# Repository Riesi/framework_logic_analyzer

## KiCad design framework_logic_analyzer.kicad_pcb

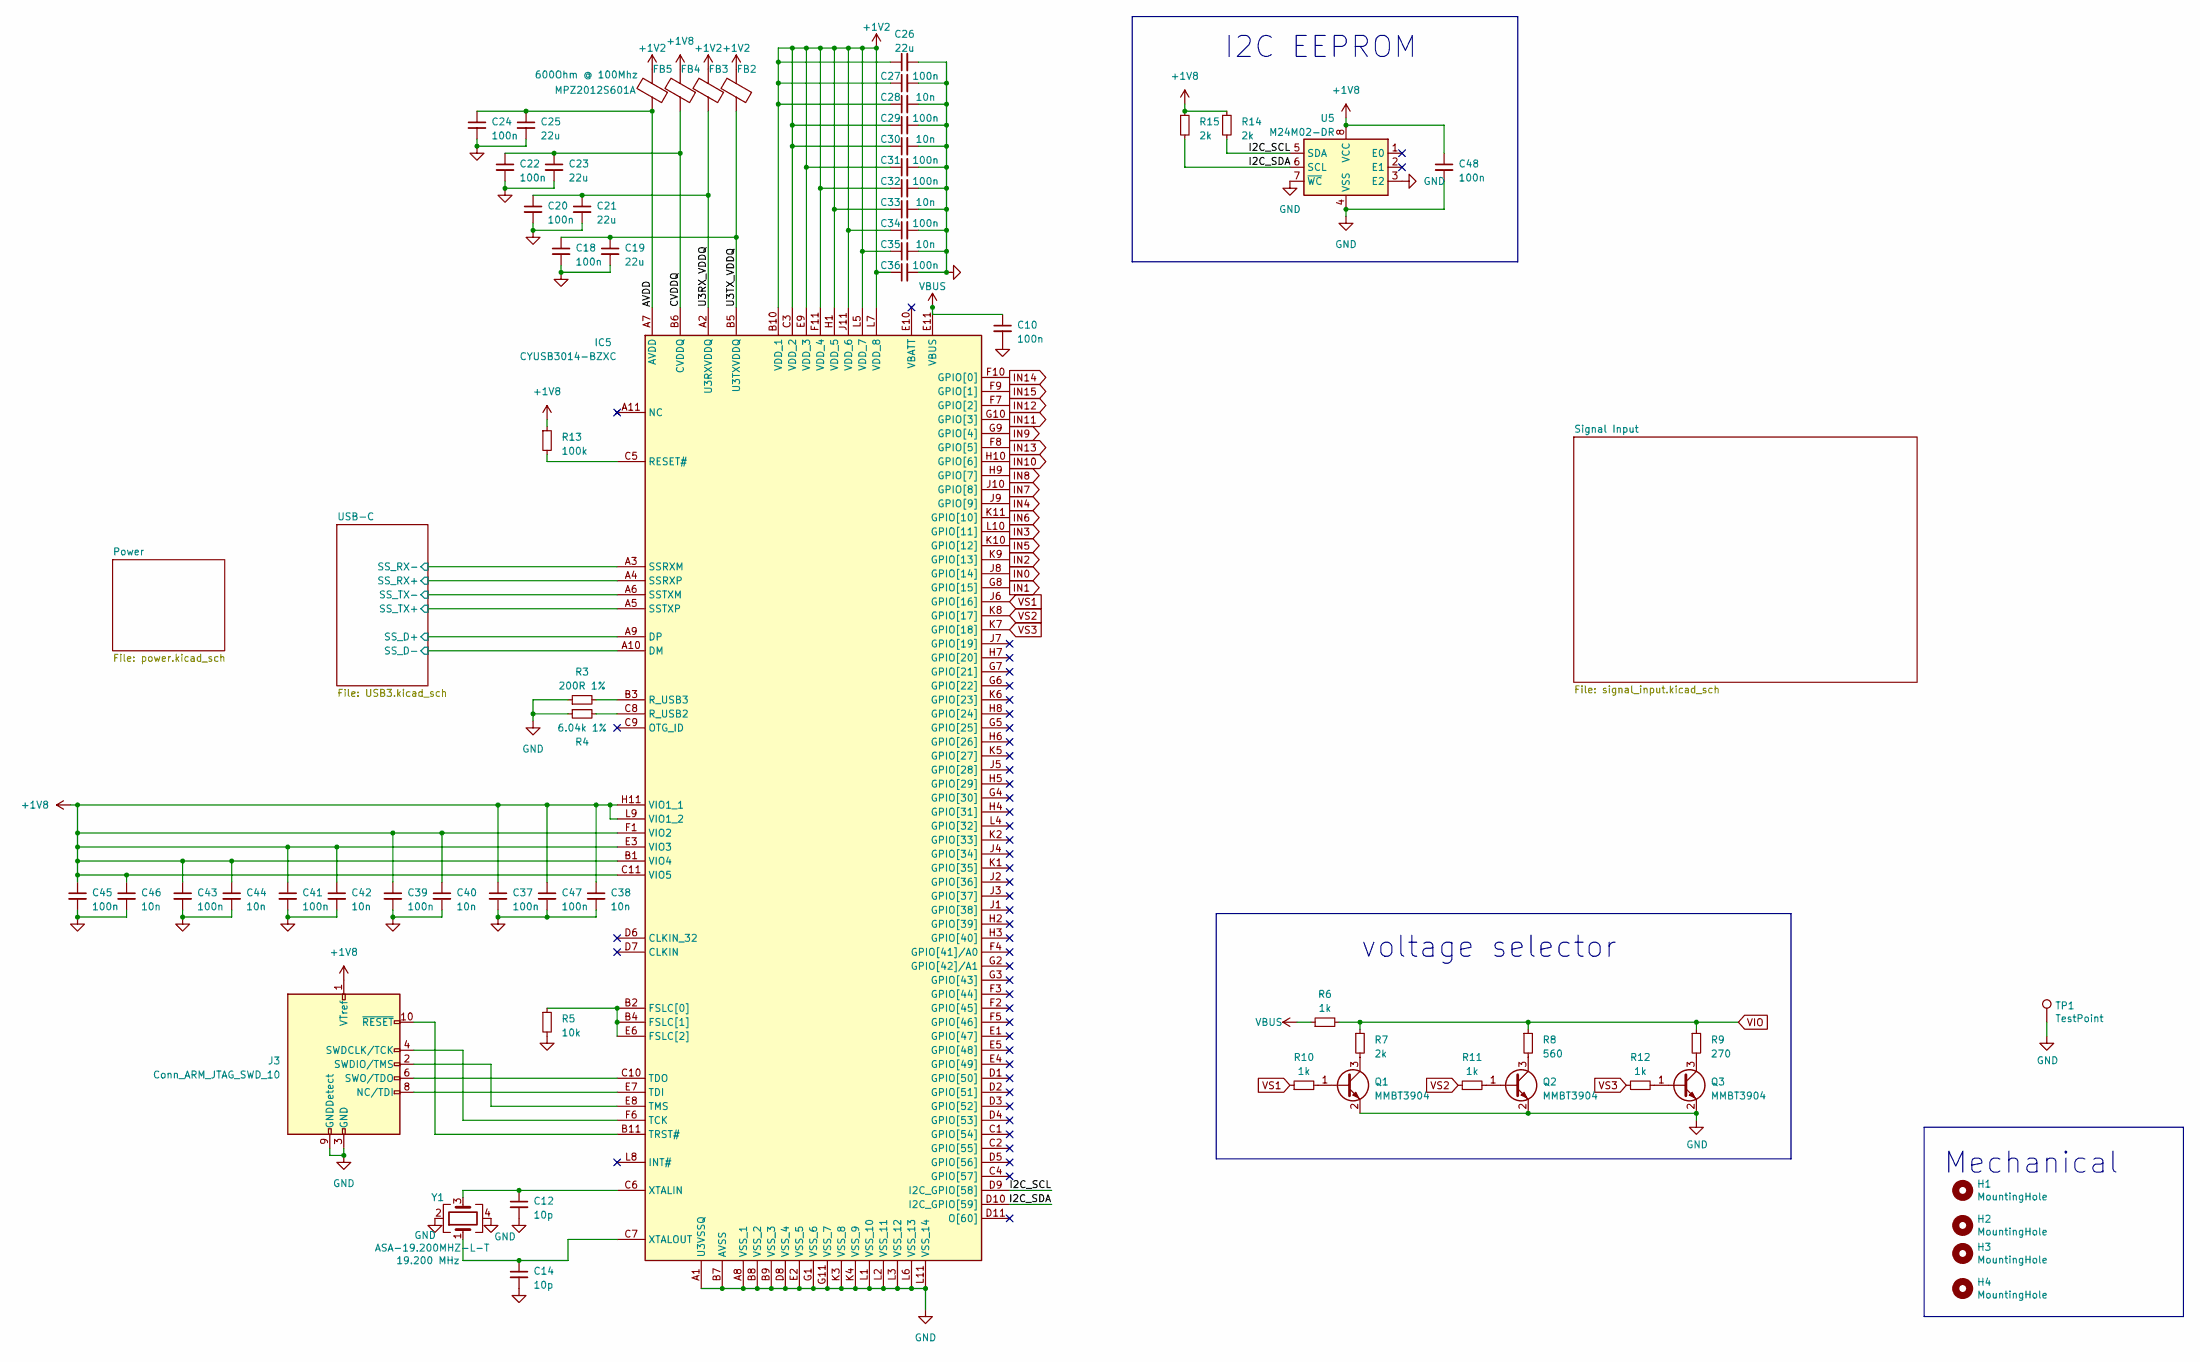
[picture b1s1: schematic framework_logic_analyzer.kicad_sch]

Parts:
C10, C18, C20, C22, C24, C27, C29, C31, C32, C34, C36, C37, C39, C41, C43, C45, C47, C48: 100n; C_0402_1005Metric
C12, C14: 10p; C_0402_1005Metric
C19, C21, C23, C25, C26: 22u; C_0603_1608Metric
C28, C30, C33, C35, C38, C40, C42, C44, C46: 10n; C_0402_1005Metric
FB2, FB3, FB4, FB5: MPZ2012S601A; L_0805_2012Metric
H1, H2, H3, H4: MountingHole; MountingHole_2.2mm_M2
IC5: CYUSB3014-BZXC; BGA121C80P11X11_1000X1000X120; Manufacturer_Part_Number CYUSB3014-BZXC; Mouser Part Number 727-CYUSB3014-BZXC
J3: Conn_ARM_JTAG_SWD_10; PinHeader_2x05_P1.27mm_Vertical
Q1, Q2, Q3: MMBT3904; SOT-23
R3: 200R 1%; R_0402_1005Metric
R4: 6.04k 1%; R_0402_1005Metric
R5: 10k; R_0402_1005Metric
R6, R10, R11, R12: 1k; R_0402_1005Metric
R7, R14, R15: 2k; R_0402_1005Metric
R8: 560; R_0402_1005Metric
R9: 270; R_0402_1005Metric
R13: 100k; R_0402_1005Metric
TP1: TestPoint; TestPoint_Pad_1.5x1.5mm
U5: M24M02-DR; SOIC-8_3.9x4.9mm_P1.27mm
Y1: 19.200 MHz; Crystal_SMD_2016-4Pin_2.0x1.6mm; mpn ASA-19.200MHZ-L-T

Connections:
+1V2: C26.1, C27.1, C28.1, C29.1, C30.1, C31.1, C32.1, C33.1, C34.1, C35.1, C36.1, FB2.2, FB3.2, FB5.2, IC5.B10 (VDD_1), IC5.C3 (VDD_2), IC5.E9 (VDD_3), IC5.F11 (VDD_4), IC5.H1 (VDD_5), IC5.J11 (VDD_6), IC5.L5 (VDD_7), IC5.L7 (VDD_8); also elsewhere on the board
+1V8: C37.1, C38.1, C39.1, C40.1, C41.1, C42.1, C43.1, C44.1, C45.1, C46.1, C47.1, C48.1, FB4.2, IC5.B1 (VIO4), IC5.C11 (VIO5), IC5.E3 (VIO3), IC5.F1 (VIO2), IC5.H11 (VIO1_1), IC5.L9 (VIO1_2), J3.1 (VTref), R13.1, R14.1, R15.1, U5.8 (VCC); also elsewhere on the board
/AVDD: C24.1, C25.1, FB5.1, IC5.A7 (AVDD)
/CVDDQ: C22.1, C23.1, FB4.1, IC5.B6 (CVDDQ)
/I2C_SCL: IC5.D9 (I2C_GPIO[58]), R14.2, U5.5 (SDA)
/I2C_SDA: IC5.D10 (I2C_GPIO[59]), R15.2, U5.6 (SCL)
/U3RX_VDDQ: C20.1, C21.1, FB3.1, IC5.A2 (U3RXVDDQ)
/U3TX_VDDQ: C18.1, C19.1, FB2.1, IC5.B5 (U3TXVDDQ)
/USB-C/SSD+: IC5.A9 (DP); also elsewhere on the board
/USB-C/SSD-: IC5.A10 (DM); also elsewhere on the board
/USB-C/SS_RX+: IC5.A4 (SSRXP); also elsewhere on the board
/USB-C/SS_RX-: IC5.A3 (SSRXM); also elsewhere on the board
/USB-C/SS_TX+: IC5.A5 (SSTXP); also elsewhere on the board
/USB-C/SS_TX-: IC5.A6 (SSTXM); also elsewhere on the board
GND: C10.2, C12.2, C14.2, C18.2, C19.2, C20.2, C21.2, C22.2, C23.2, C24.2, C25.2, C26.2, C27.2, C28.2, C29.2, C30.2, C31.2, C32.2, C33.2, C34.2, C35.2, C36.2, C37.2, C38.2, C39.2, C40.2, C41.2, C42.2, C43.2, C44.2, C45.2, C46.2, C47.2, C48.2, IC5.A1 (U3VSSQ), IC5.A8 (VSS_1), IC5.B7 (AVSS), IC5.B8 (VSS_2), IC5.B9 (VSS_3), IC5.D8 (VSS_4), IC5.E2 (VSS_5), IC5.G1 (VSS_6), IC5.G11 (VSS_7), IC5.K3 (VSS_8), IC5.K4 (VSS_9), IC5.L1 (VSS_10), IC5.L2 (VSS_11), IC5.L3 (VSS_12), IC5.L6 (VSS_13), IC5.L11 (VSS_14), J3.3 (GND), J3.5 (GND), J3.9 (GNDDetect), Q1.2 (E), Q2.2 (E), Q3.2 (E), R3.1, R4.1, R5.2, TP1.1, U5.3 (E2), U5.4 (VSS), U5.7 (~WC), Y1.2, Y1.4; also elsewhere on the board
IN0: IC5.J8 (GPIO[14]); also elsewhere on the board
IN1: IC5.G8 (GPIO[15]); also elsewhere on the board
IN2: IC5.K9 (GPIO[13]); also elsewhere on the board
IN3: IC5.L10 (GPIO[11]); also elsewhere on the board
IN4: IC5.J9 (GPIO[9]); also elsewhere on the board
IN5: IC5.K10 (GPIO[12]); also elsewhere on the board
IN6: IC5.K11 (GPIO[10]); also elsewhere on the board
IN7: IC5.J10 (GPIO[8]); also elsewhere on the board
IN8: IC5.H9 (GPIO[7]); also elsewhere on the board
IN9: IC5.G9 (GPIO[4]); also elsewhere on the board
IN10: IC5.H10 (GPIO[6]); also elsewhere on the board
IN11: IC5.G10 (GPIO[3]); also elsewhere on the board
IN12: IC5.F7 (GPIO[2]); also elsewhere on the board
IN13: IC5.F8 (GPIO[5]); also elsewhere on the board
IN14: IC5.F10 (GPIO[0]); also elsewhere on the board
IN15: IC5.F9 (GPIO[1]); also elsewhere on the board
unnamed: IC5.B2 (FSLC[0]), IC5.B4 (FSLC[1]), IC5.E6 (FSLC[2]), R5.1
unnamed: IC5.C5 (RESET#), R13.2
unnamed: IC5.C8 (R_USB2), R4.2
unnamed: IC5.B3 (R_USB3), R3.2
unnamed: IC5.F6 (TCK), J3.4 (SWDCLK/TCK)
unnamed: IC5.E7 (TDI), J3.8 (NC/TDI)
unnamed: IC5.C10 (TDO), J3.6 (SWO/TDO)
unnamed: IC5.E8 (TMS), J3.2 (SWDIO/TMS)
unnamed: IC5.B11 (TRST#), J3.10 (~RESET)
unnamed: C12.1, IC5.C6 (XTALIN), Y1.3
unnamed: C14.1, IC5.C7 (XTALOUT), Y1.1
unnamed: Q1.1 (B), R10.2
unnamed: Q1.3 (C), R7.2
unnamed: Q2.1 (B), R11.2
unnamed: Q2.3 (C), R8.2
unnamed: Q3.1 (B), R12.2
unnamed: Q3.3 (C), R9.2
VBUS: C10.1, IC5.E11 (VBUS), R6.1; also elsewhere on the board
VIO: R6.2, R7.1, R8.1, R9.1; also elsewhere on the board
VS1: IC5.J6 (GPIO[16]), R10.1
VS2: IC5.K8 (GPIO[17]), R11.1
VS3: IC5.K7 (GPIO[18]), R12.1

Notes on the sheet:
voltage selector
I2C EEPROM
Mechanical

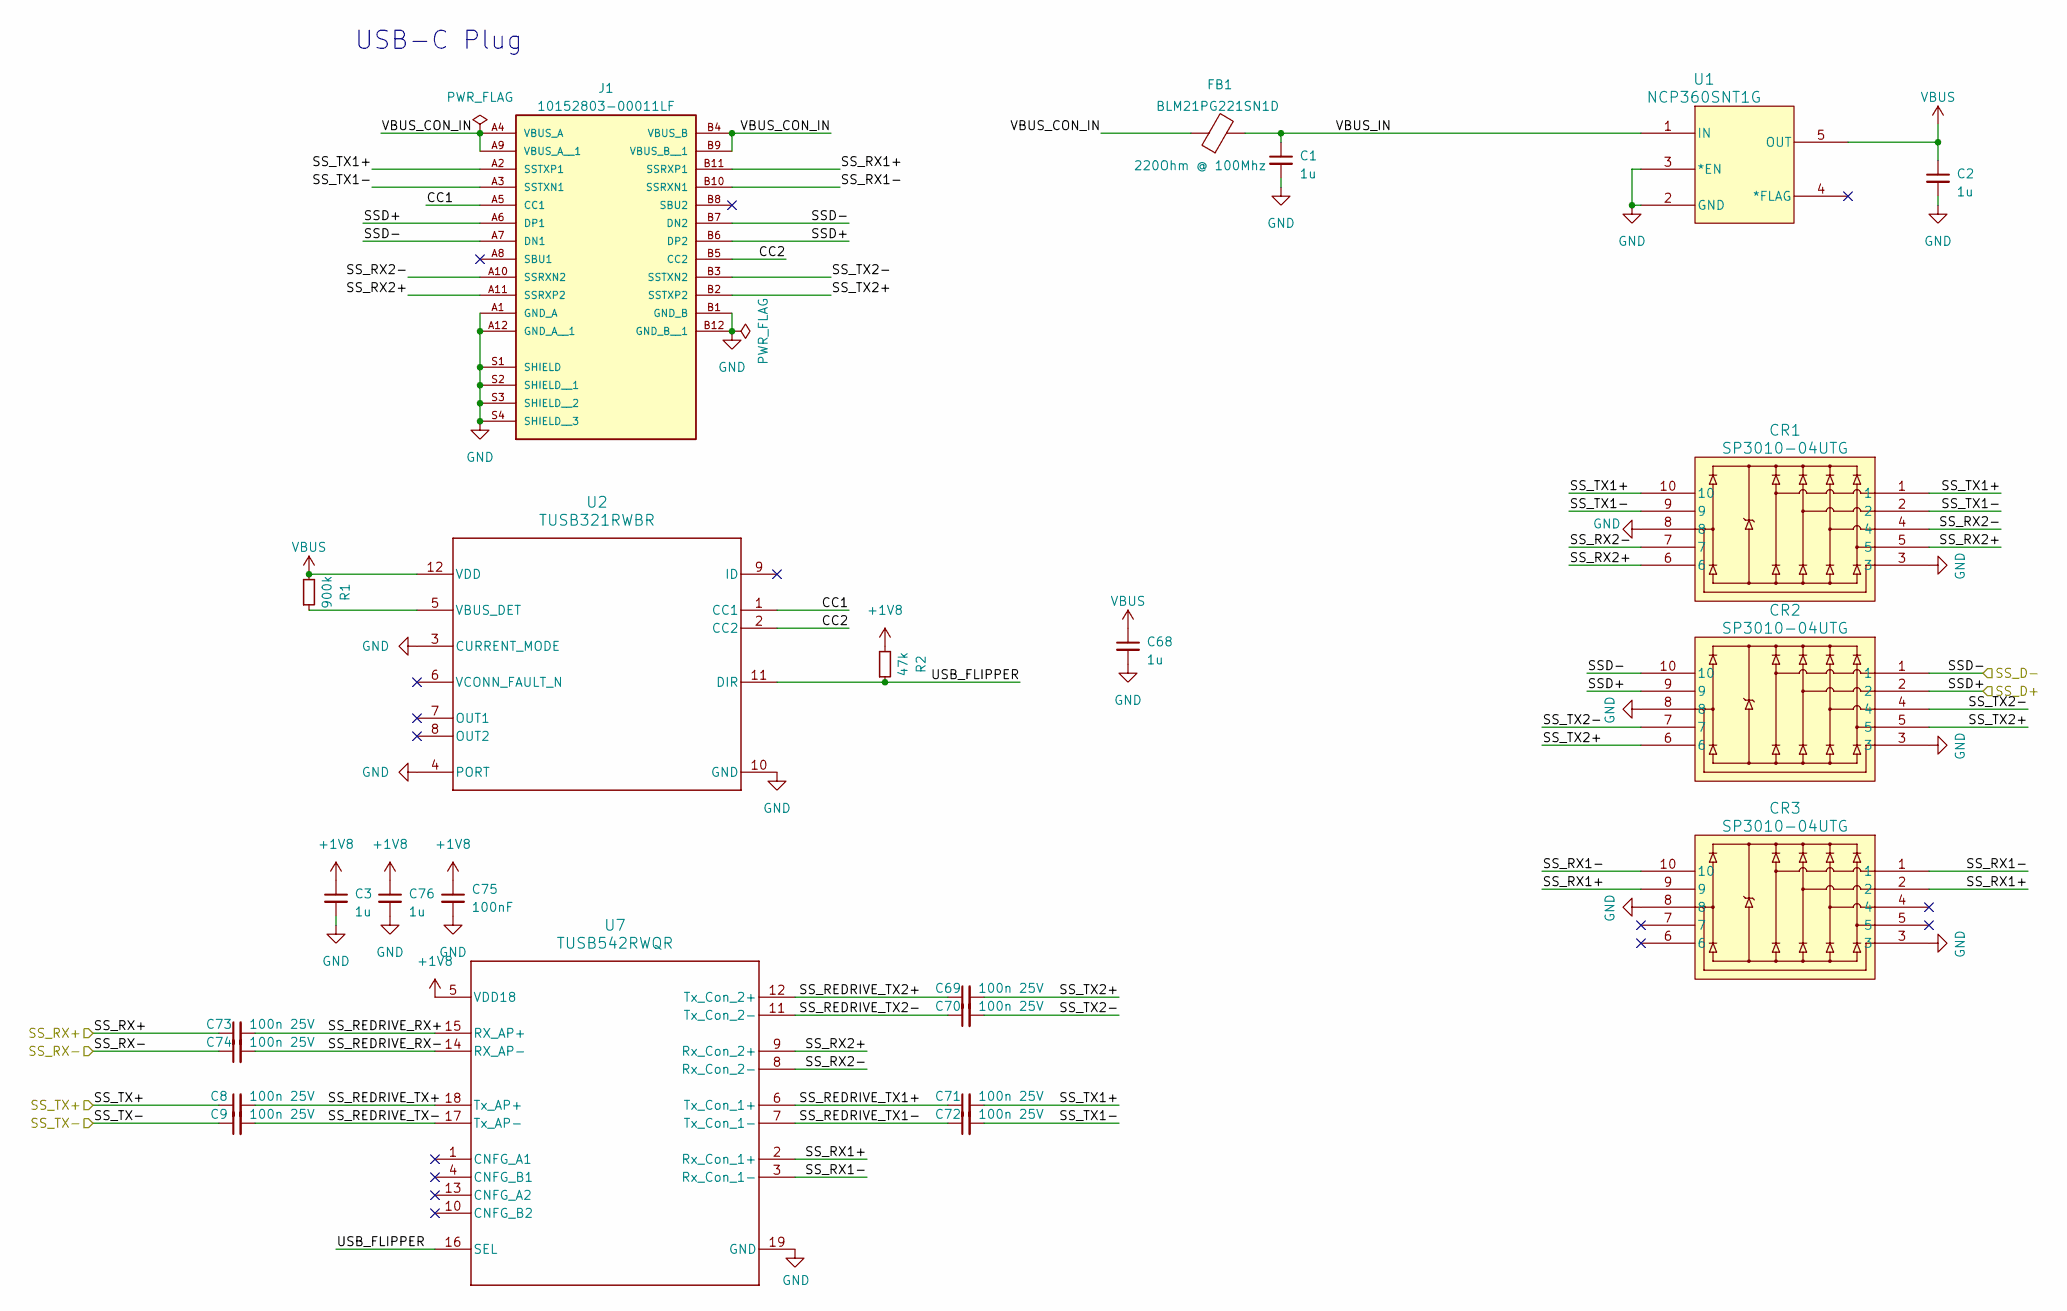
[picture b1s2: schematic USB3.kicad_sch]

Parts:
C1, C2, C3, C68, C76: 1u; C_0402_1005Metric
C8, C9, C69, C70, C71, C72, C73, C74: 100n 25V; C_0201_0603Metric_USB
C75: 100nF; C_0402_1005Metric
CR1, CR2, CR3: SP3010-04UTG; UDFEN-10_MO229_LTF
FB1: BLM21PG221SN1D; L_0805_2012Metric
J1: 10152803-00011LF; 10152803-00011LF_AMPHENOL_10152803-00011LF; PARTREV A
R1: 900k; R_0402_1005Metric
R2: 47k; R_0402_1005Metric
U1: NCP360SNT1G; TSOP5_3X1P5_ONS
U2: TUSB321RWBR; RWB0012A
U7: TUSB542RWQR; RWQ0018A

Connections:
+1V8: C3.1, C75.1, C76.1, R2.2, U7.5 (VDD18); also elsewhere on the board
/USB-C/CC1: J1.A5 (CC1), U2.1 (CC1)
/USB-C/CC2: J1.B5 (CC2), U2.2 (CC2)
/USB-C/SSD+: CR2.2, CR2.9, J1.A6 (DP1), J1.B6 (DP2); also elsewhere on the board
/USB-C/SSD-: CR2.1, CR2.10, J1.A7 (DN1), J1.B7 (DN2); also elsewhere on the board
/USB-C/SS_REDRIVE_RX+: C73.2, U7.15 (RX_AP+)
/USB-C/SS_REDRIVE_RX-: C74.2, U7.14 (RX_AP-)
/USB-C/SS_REDRIVE_TX1+: C71.1, U7.6 (Tx_Con_1+)
/USB-C/SS_REDRIVE_TX1-: C72.1, U7.7 (Tx_Con_1-)
/USB-C/SS_REDRIVE_TX2+: C69.1, U7.12 (Tx_Con_2+)
/USB-C/SS_REDRIVE_TX2-: C70.1, U7.11 (Tx_Con_2-)
/USB-C/SS_REDRIVE_TX+: C8.2, U7.18 (Tx_AP+)
/USB-C/SS_REDRIVE_TX-: C9.2, U7.17 (Tx_AP-)
/USB-C/SS_RX1+: CR3.2, CR3.9, J1.B11 (SSRXP1), U7.2 (Rx_Con_1+)
/USB-C/SS_RX1-: CR3.1, CR3.10, J1.B10 (SSRXN1), U7.3 (Rx_Con_1-)
/USB-C/SS_RX2+: CR1.5, CR1.6, J1.A11 (SSRXP2), U7.9 (Rx_Con_2+)
/USB-C/SS_RX2-: CR1.4, CR1.7, J1.A10 (SSRXN2), U7.8 (Rx_Con_2-)
/USB-C/SS_RX+: C73.1; also elsewhere on the board
/USB-C/SS_RX-: C74.1; also elsewhere on the board
/USB-C/SS_TX1+: C71.2, CR1.1, CR1.10, J1.A2 (SSTXP1)
/USB-C/SS_TX1-: C72.2, CR1.2, CR1.9, J1.A3 (SSTXN1)
/USB-C/SS_TX2+: C69.2, CR2.5, CR2.6, J1.B2 (SSTXP2)
/USB-C/SS_TX2-: C70.2, CR2.4, CR2.7, J1.B3 (SSTXN2)
/USB-C/SS_TX+: C8.1; also elsewhere on the board
/USB-C/SS_TX-: C9.1; also elsewhere on the board
/USB-C/USB_FLIPPER: R2.1, U2.11 (DIR), U7.16 (SEL)
/USB-C/VBUS_CON_IN: FB1.1, J1.A4 (VBUS_A), J1.A9 (VBUS_A__1), J1.B4 (VBUS_B), J1.B9 (VBUS_B__1)
/USB-C/VBUS_IN: C1.1, FB1.2, U1.1 (IN)
GND: C1.2, C2.2, C3.2, C68.2, C75.2, C76.2, CR1.3, CR1.8, CR2.3, CR2.8, CR3.3, CR3.8, J1.A1 (GND_A), J1.A12 (GND_A__1), J1.B1 (GND_B), J1.B12 (GND_B__1), J1.S1 (SHIELD), J1.S2 (SHIELD__1), J1.S3 (SHIELD__2), J1.S4 (SHIELD__3), U1.2 (GND), U1.3 (*EN), U2.3 (CURRENT_MODE), U2.4 (PORT), U2.10 (GND), U7.19 (GND); also elsewhere on the board
unnamed: R1.1, U2.5 (VBUS_DET)
VBUS: C2.1, C68.1, R1.2, U1.5 (OUT), U2.12 (VDD); also elsewhere on the board

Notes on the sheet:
USB-C Plug

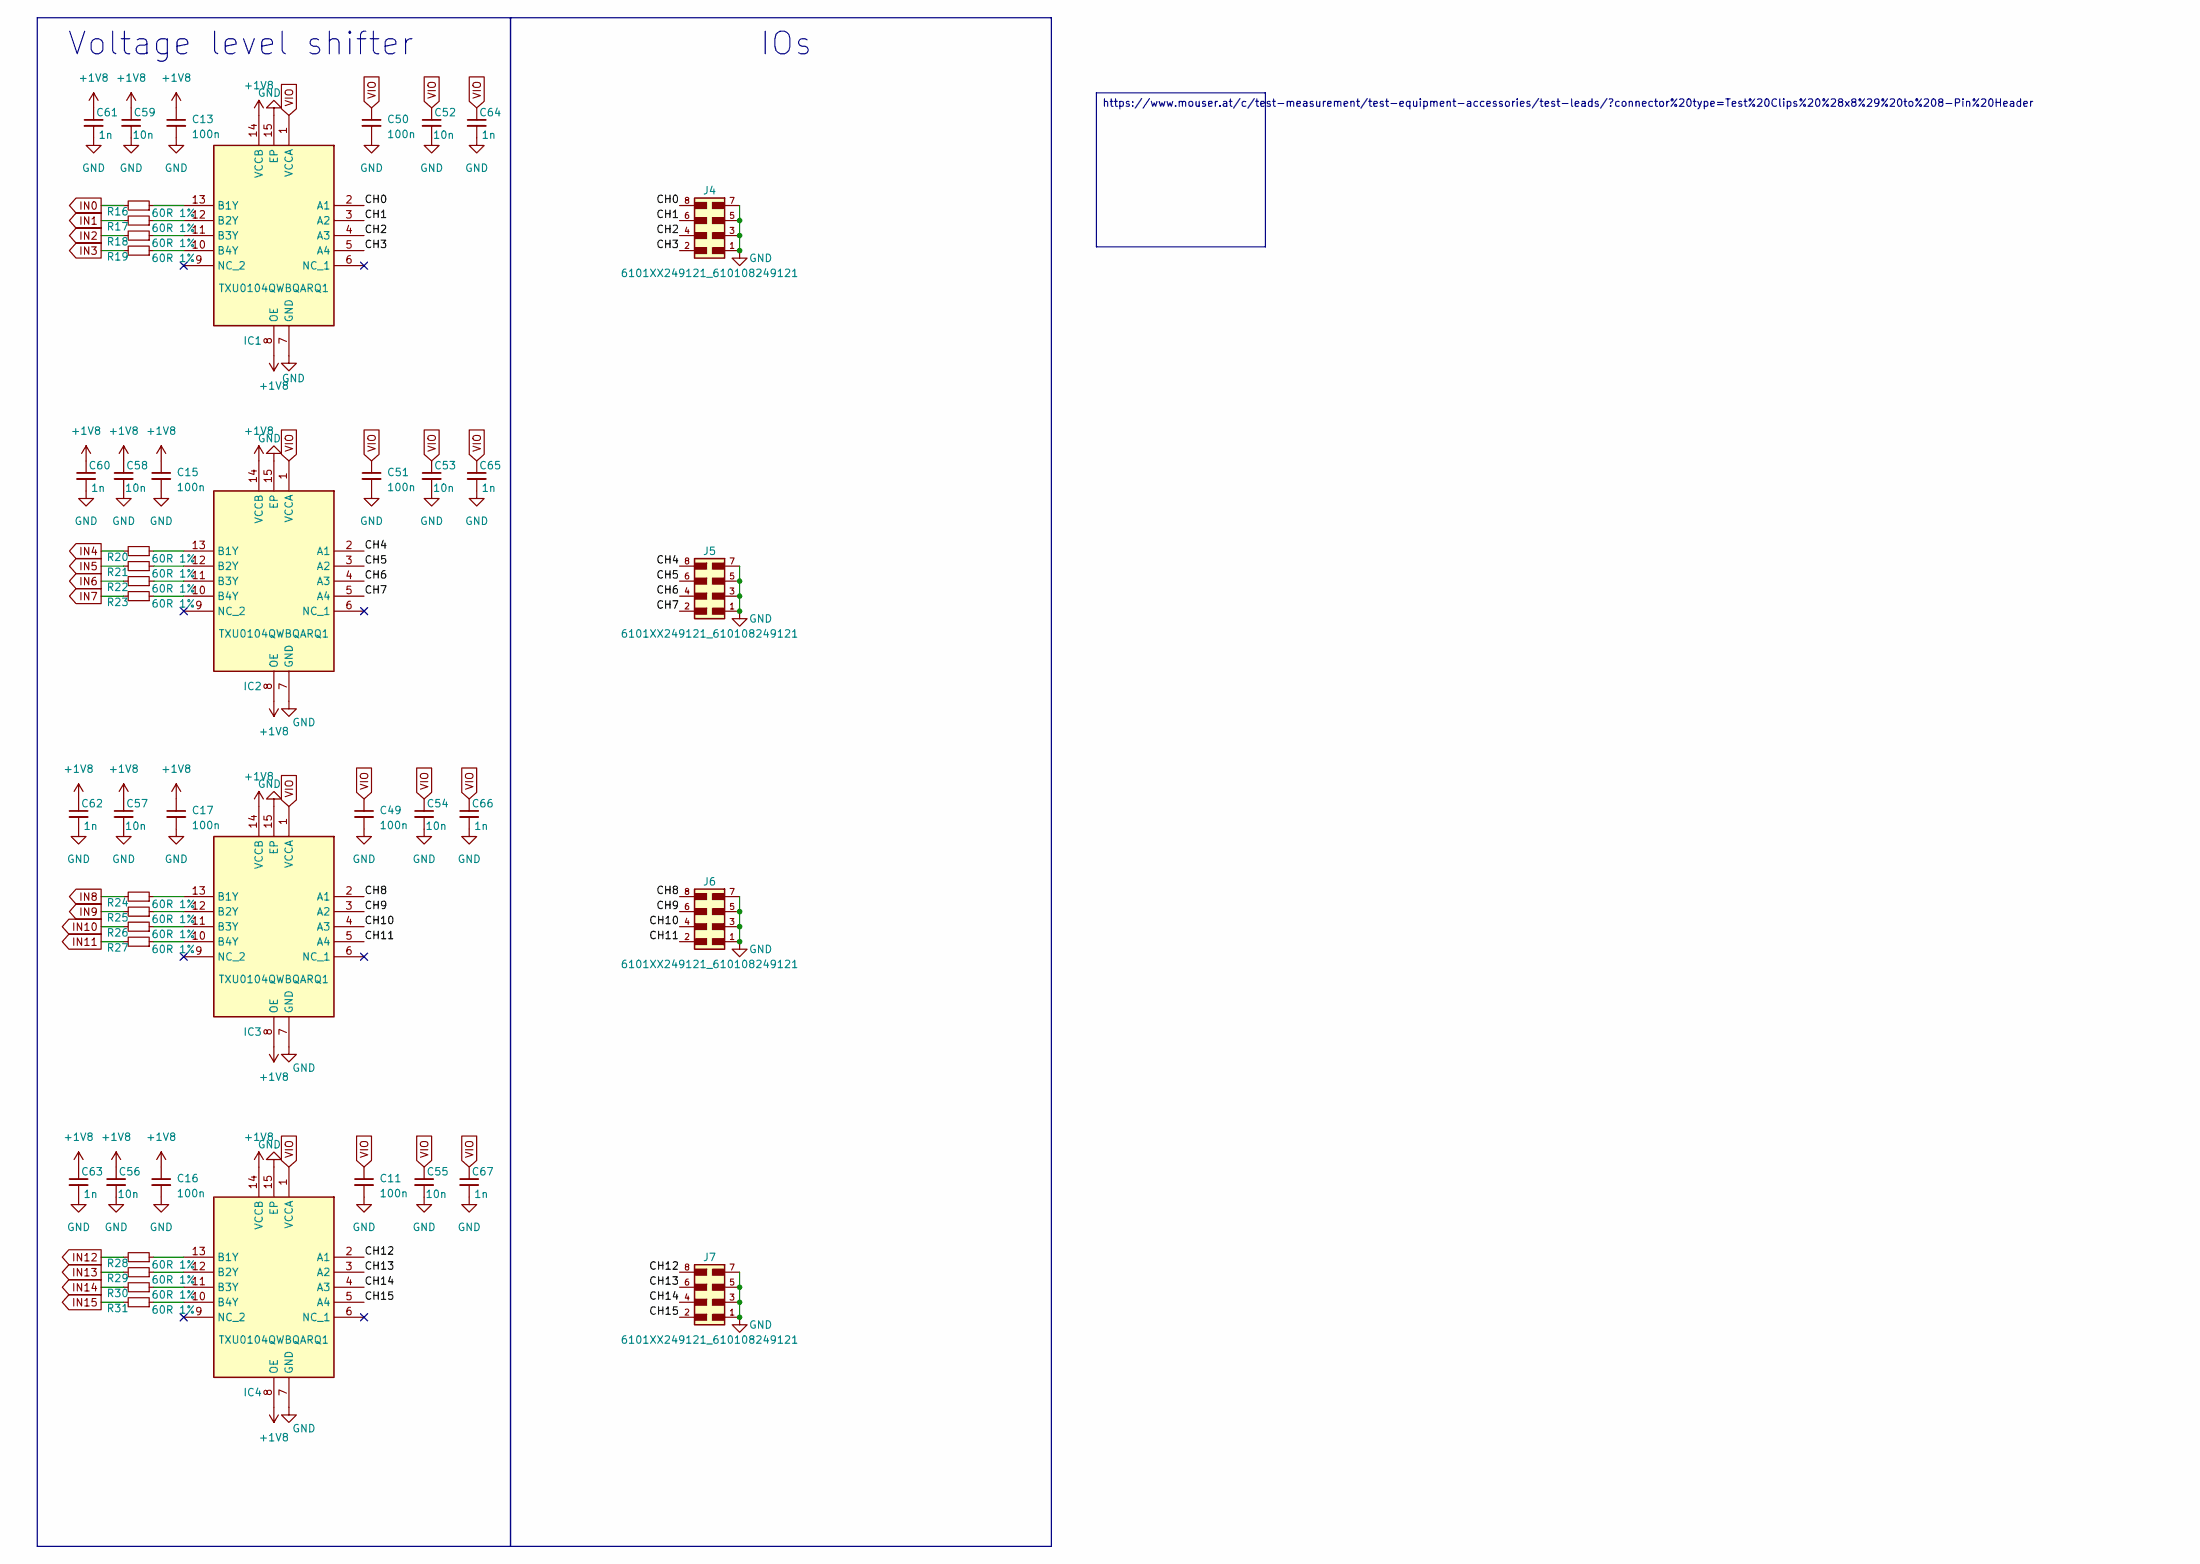
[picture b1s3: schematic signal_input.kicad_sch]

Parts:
C11, C13, C15, C16, C17, C49, C50, C51: 100n; C_0402_1005Metric
C52, C53, C54, C55, C56, C57, C58, C59: 10n; C_0402_1005Metric
C60, C61, C62, C63, C64, C65, C66, C67: 1n; C_0402_1005Metric
IC1, IC2, IC3, IC4: TXU0104QWBQARQ1; Manufacturer_Part_Number TXU0104QWBQARQ1; Mouser Part Number 595-TXU0104QWBQARQ1
J4, J5, J6, J7: 6101XX249121_610108249121; 6101XX249121_610108249121_610108249121
R16, R17, R18, R19, R20, R21, R22, R23, R24, R25, R26, R27, R28, R29, R30, R31: 60R 1%; R_0201_0603Metric_input

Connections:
+1V8: C13.1, C15.1, C16.1, C17.1, C56.1, C57.1, C58.1, C59.1, C60.1, C61.1, C62.1, C63.1, IC1.8 (OE), IC1.14 (VCCB), IC2.8 (OE), IC2.14 (VCCB), IC3.8 (OE), IC3.14 (VCCB), IC4.8 (OE), IC4.14 (VCCB); also elsewhere on the board
/Signal Input/CH0: IC1.2 (A1), J4.8
/Signal Input/CH1: IC1.3 (A2), J4.6
/Signal Input/CH2: IC1.4 (A3), J4.4
/Signal Input/CH3: IC1.5 (A4), J4.2
/Signal Input/CH4: IC2.2 (A1), J5.8
/Signal Input/CH5: IC2.3 (A2), J5.6
/Signal Input/CH6: IC2.4 (A3), J5.4
/Signal Input/CH7: IC2.5 (A4), J5.2
/Signal Input/CH8: IC3.2 (A1), J6.8
/Signal Input/CH9: IC3.3 (A2), J6.6
/Signal Input/CH10: IC3.4 (A3), J6.4
/Signal Input/CH11: IC3.5 (A4), J6.2
/Signal Input/CH12: IC4.2 (A1), J7.8
/Signal Input/CH13: IC4.3 (A2), J7.6
/Signal Input/CH14: IC4.4 (A3), J7.4
/Signal Input/CH15: IC4.5 (A4), J7.2
GND: C11.2, C13.2, C15.2, C16.2, C17.2, C49.2, C50.2, C51.2, C52.2, C53.2, C54.2, C55.2, C56.2, C57.2, C58.2, C59.2, C60.2, C61.2, C62.2, C63.2, C64.2, C65.2, C66.2, C67.2, IC1.7 (GND), IC1.15 (EP), IC2.7 (GND), IC2.15 (EP), IC3.7 (GND), IC3.15 (EP), IC4.7 (GND), IC4.15 (EP), J4.1, J4.3, J4.5, J4.7, J5.1, J5.3, J5.5, J5.7, J6.1, J6.3, J6.5, J6.7, J7.1, J7.3, J7.5, J7.7; also elsewhere on the board
IN0: R16.2; also elsewhere on the board
IN1: R17.2; also elsewhere on the board
IN2: R18.2; also elsewhere on the board
IN3: R19.2; also elsewhere on the board
IN4: R20.2; also elsewhere on the board
IN5: R21.2; also elsewhere on the board
IN6: R22.2; also elsewhere on the board
IN7: R23.2; also elsewhere on the board
IN8: R24.2; also elsewhere on the board
IN9: R25.2; also elsewhere on the board
IN10: R26.2; also elsewhere on the board
IN11: R27.2; also elsewhere on the board
IN12: R28.2; also elsewhere on the board
IN13: R29.2; also elsewhere on the board
IN14: R30.2; also elsewhere on the board
IN15: R31.2; also elsewhere on the board
unnamed: IC1.13 (B1Y), R16.1
unnamed: IC1.12 (B2Y), R17.1
unnamed: IC1.11 (B3Y), R18.1
unnamed: IC1.10 (B4Y), R19.1
unnamed: IC2.13 (B1Y), R20.1
unnamed: IC2.12 (B2Y), R21.1
unnamed: IC2.11 (B3Y), R22.1
unnamed: IC2.10 (B4Y), R23.1
unnamed: IC3.13 (B1Y), R24.1
unnamed: IC3.12 (B2Y), R25.1
unnamed: IC3.11 (B3Y), R26.1
unnamed: IC3.10 (B4Y), R27.1
unnamed: IC4.13 (B1Y), R28.1
unnamed: IC4.12 (B2Y), R29.1
unnamed: IC4.11 (B3Y), R30.1
unnamed: IC4.10 (B4Y), R31.1
VIO: C11.1, C49.1, C50.1, C51.1, C52.1, C53.1, C54.1, C55.1, C64.1, C65.1, C66.1, C67.1, IC1.1 (VCCA), IC2.1 (VCCA), IC3.1 (VCCA), IC4.1 (VCCA); also elsewhere on the board

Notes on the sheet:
Voltage level shifter
IOs
https://www.mouser.at/c/test-measurement/test-equipment-accessories/test-leads/?connector%20type=Test%20Clips%20%28x8%29%20to%208-Pin%20Header

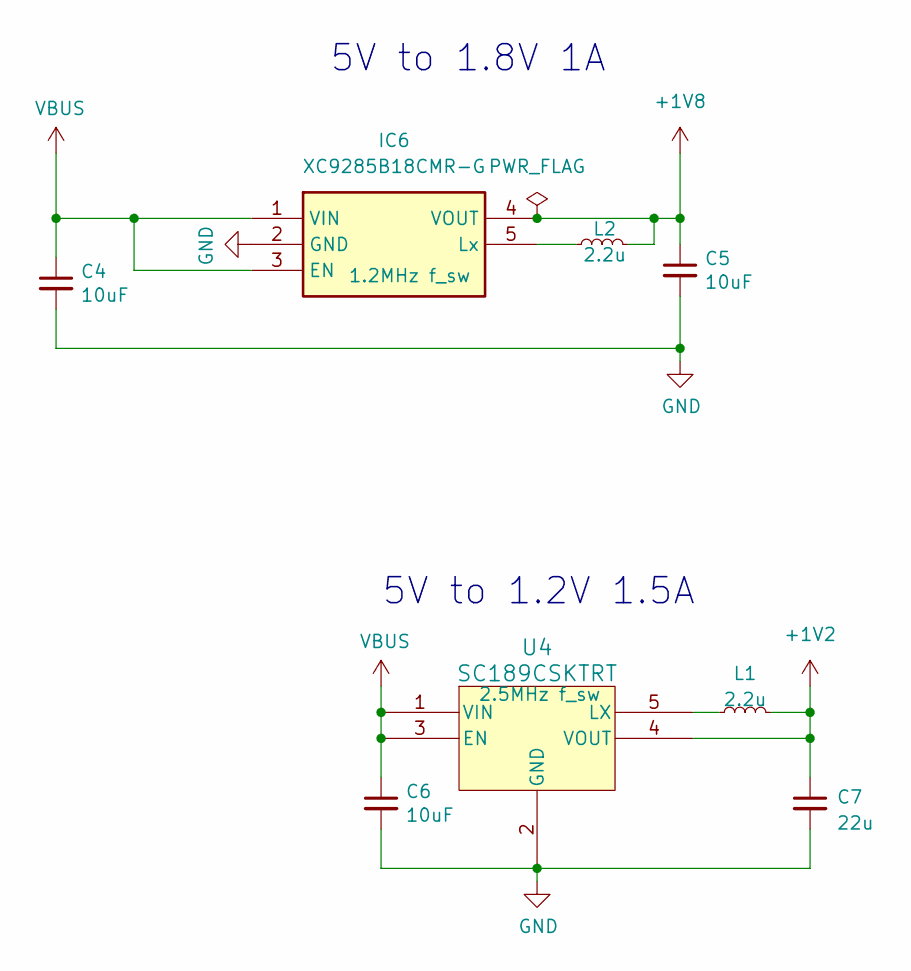
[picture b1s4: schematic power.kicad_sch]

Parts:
C4, C5, C6: 10uF; C_0805_2012Metric
C7: 22u; C_0603_1608Metric
IC6: XC9285B18CMR-G; SOT95P280X130-5N; Manufacturer_Part_Number XC9285B18CMR-G
L1, L2: 2.2u; L_1008_2520Metric; LCSC C315721
U4: SC189CSKTRT; SOT_CSKTRT_SEM

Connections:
+1V2: C7.1, L1.2, U4.4 (VOUT); also elsewhere on the board
+1V8: C5.1, IC6.4 (VOUT), L2.2; also elsewhere on the board
GND: C4.2, C5.2, C6.2, C7.2, IC6.2 (GND), U4.2 (GND); also elsewhere on the board
unnamed: IC6.5 (Lx), L2.1
unnamed: L1.1, U4.5 (LX)
VBUS: C4.1, C6.1, IC6.1 (VIN), IC6.3 (EN), U4.1 (VIN), U4.3 (EN); also elsewhere on the board

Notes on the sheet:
5V to 1.8V 1A
5V to 1.2V 1.5A

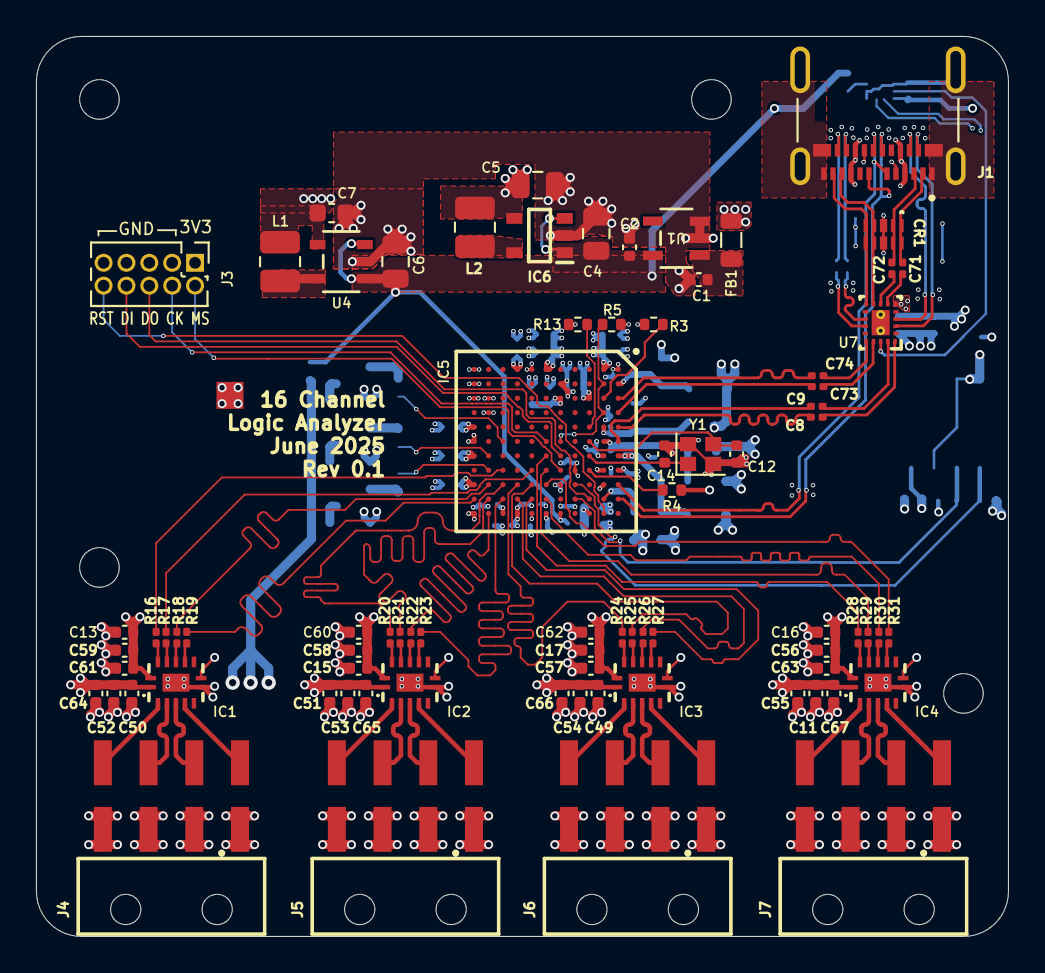
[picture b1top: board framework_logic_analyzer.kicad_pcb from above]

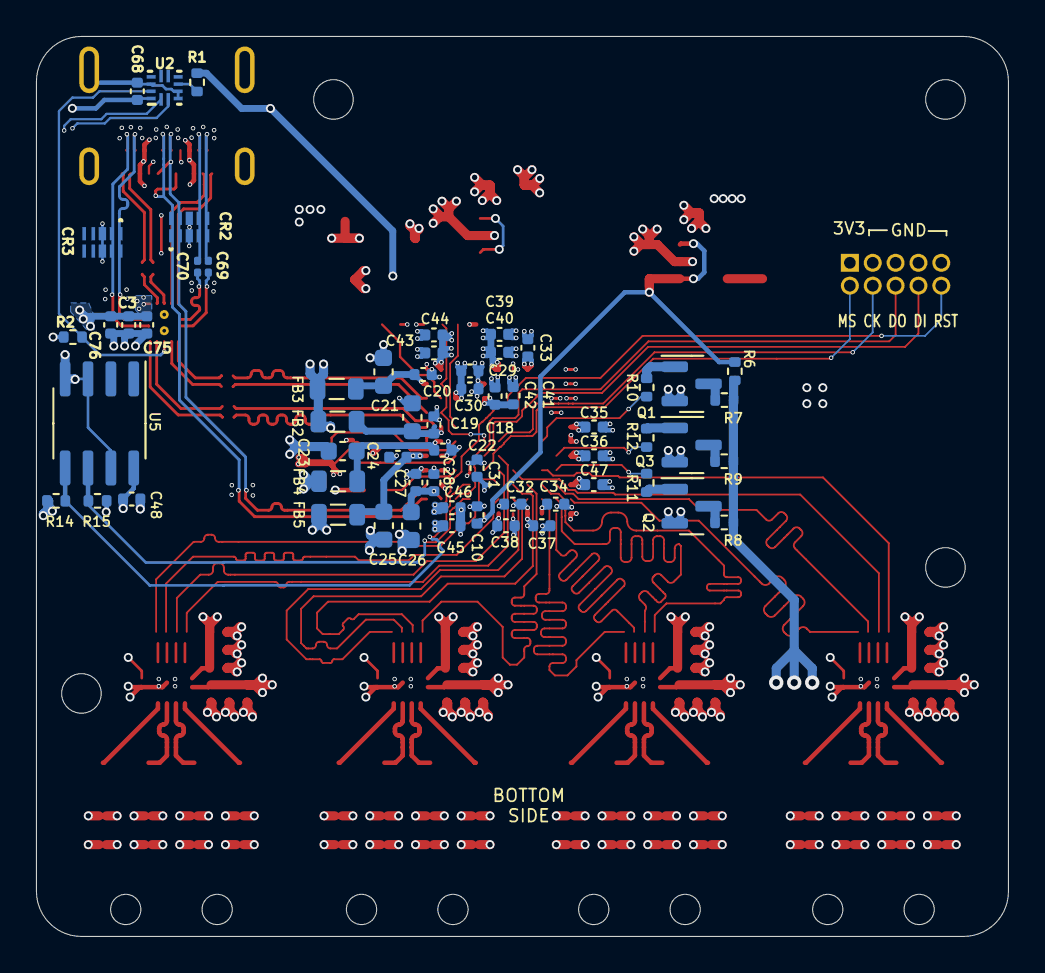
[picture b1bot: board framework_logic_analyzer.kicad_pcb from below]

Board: 6 copper layers, 54.0 x 50.0 mm, 143 parts (60 on the bottom side), 109 nets.

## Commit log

2025-05-15 update to kicad 9
2025-06-07 begin big refactor
2025-06-07 more work
2025-06-08 further routing
2025-06-09 more routing, add differential pair netclass
2025-06-09 length match input channels
2025-06-09 begin USB3 layouting ...
2025-06-10 add usb3 redriver
2025-06-10 change usb c plug
2025-06-12 implement USB3.0 active redriver and fix DRC errors
2025-06-12 add USB time matching
2025-06-12 add AC caps for redriver; fix ERC and DRC errors
2025-06-17 initial TurboCase implementation
2025-06-18 start reworking the usb3c to add ESD and better impedance matching
2025-06-20 start implementing SML feedback
2025-06-24 commit data
2025-06-26 implement all SML review nits
    hopefully
2025-06-26 ground plane to the max!
2025-06-26 length matching on usb
